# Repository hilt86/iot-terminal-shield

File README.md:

# iot-terminal-shield
Terminal Shield for Photon / Electron / Lopy 

This is a shield that allows you to mount a Particle.io Photon / Electron or a pycom.io Lopy / Wipy and use screw
terminals to connect to the board pins instead of jumpers which can be quite flaky, especially if you want to move the board around which is often the case with IoT projects.

I am new to Eagle so this is a first attempt and hence the board is ugly and not even square. However I have had this baord fabricated and it does work. It also has the parts for the screw terminals and headers if you don't want to solder those on by hand.

Submit a pull request if you want to improve the board..

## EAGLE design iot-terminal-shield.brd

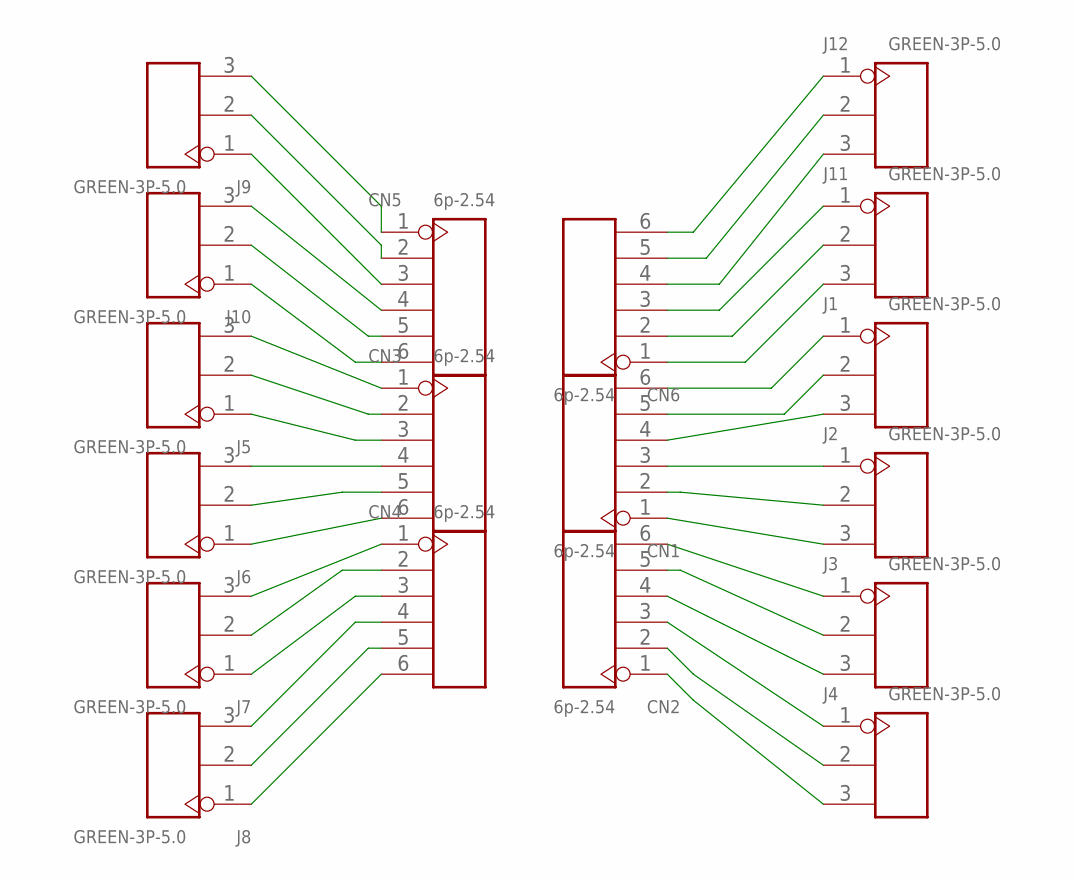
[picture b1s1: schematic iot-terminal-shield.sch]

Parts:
CN1, CN2, CN3, CN4, CN5, CN6: 6p-2.54; H6-2.54
J1, J2, J3, J4, J5, J6, J7, J8, J9, J10, J11, J12: GREEN-3P-5.0; H3-5.0-15.5X8.0MM

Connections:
unnamed: CN3.1, J5.3
unnamed: CN3.2, J5.2
unnamed: CN3.3, J5.1
unnamed: CN3.4, J6.3
unnamed: CN3.5, J6.2
unnamed: CN3.6, J6.1
unnamed: CN4.1, J7.3
unnamed: CN4.2, J7.2
unnamed: CN4.3, J7.1
unnamed: CN4.4, J8.3
unnamed: CN4.5, J8.2
unnamed: CN4.6, J8.1
unnamed: CN1.6, J1.1
unnamed: CN1.5, J1.2
unnamed: CN1.4, J1.3
unnamed: CN1.3, J2.1
unnamed: CN1.2, J2.2
unnamed: CN1.1, J2.3
unnamed: CN2.6, J3.1
unnamed: CN2.5, J3.2
unnamed: CN2.4, J3.3
unnamed: CN2.3, J4.1
unnamed: CN2.2, J4.2
unnamed: CN2.1, J4.3
unnamed: CN5.6, J10.1
unnamed: CN5.5, J10.2
unnamed: CN5.4, J10.3
unnamed: CN6.1, J11.3
unnamed: CN6.2, J11.2
unnamed: CN6.3, J11.1
unnamed: CN6.4, J12.3
unnamed: CN6.5, J12.2
unnamed: CN6.6, J12.1
unnamed: CN5.3, J9.1
unnamed: CN5.2, J9.2
unnamed: CN5.1, J9.3

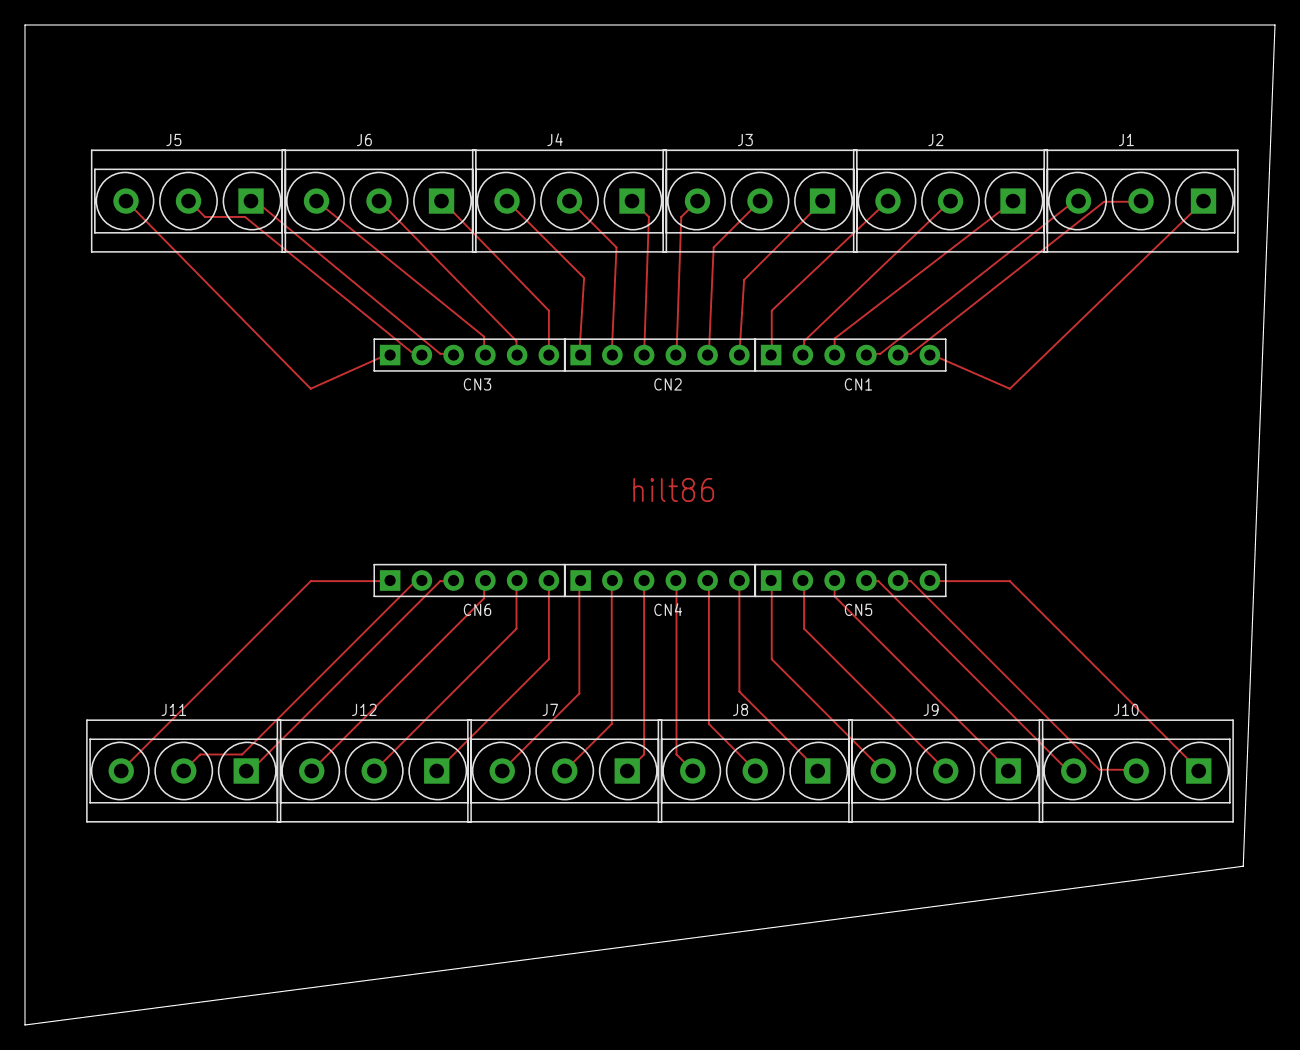
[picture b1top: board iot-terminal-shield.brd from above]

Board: 2 copper layers, 100.0 x 80.0 mm, 18 parts (0 on the bottom side), 36 nets.

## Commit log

2017-12-06 Terminal shield for Photon / Electron / Lopy - board has been printed and tested
